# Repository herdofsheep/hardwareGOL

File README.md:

# hardwareGOL
Arduino code to run the game of life on an LED multiplex.

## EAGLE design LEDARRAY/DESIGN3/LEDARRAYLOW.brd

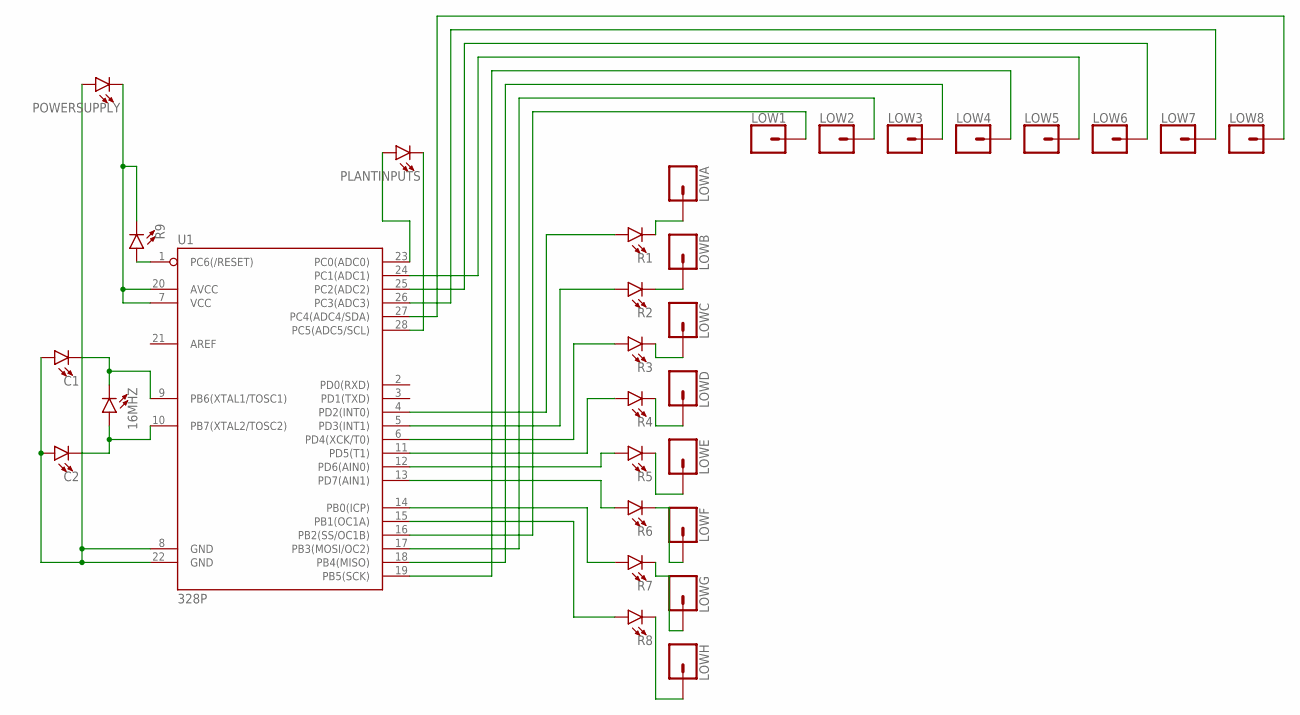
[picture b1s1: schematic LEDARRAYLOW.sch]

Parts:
16MHZ: LED3MM; LED_3MM
C1, C2: LED3MM; LED_3MM
LOW1, LOW2, LOW3, LOW4, LOW5, LOW6, LOW7, LOW8: CONN_01PTH_NO_SILK_KIT; 1X01NS_KIT
LOWA: CONN_01PTH_NO_SILK_KIT; 1X01NS_KIT
LOWB: CONN_01PTH_NO_SILK_KIT; 1X01NS_KIT
LOWC: CONN_01PTH_NO_SILK_KIT; 1X01NS_KIT
LOWD: CONN_01PTH_NO_SILK_KIT; 1X01NS_KIT
LOWE: CONN_01PTH_NO_SILK_KIT; 1X01NS_KIT
LOWF: CONN_01PTH_NO_SILK_KIT; 1X01NS_KIT
LOWG: CONN_01PTH_NO_SILK_KIT; 1X01NS_KIT
LOWH: CONN_01PTH_NO_SILK_KIT; 1X01NS_KIT
PLANTINPUTS: LED3MM; LED_3MM
POWERSUPPLY: LED3MM; LED_3MM
R1, R2, R3, R4, R5, R6, R7, R8, R9: LED3MM; LED_3MM
U1: 328P; DIP28

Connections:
LEDD1: LOW1.1, U1.16 (PB2(SS/OC1B))
unnamed: R8.A, U1.15 (PB1(OC1A))
unnamed: LOWD.1, R4.K (C)
unnamed: R6.A, U1.13 (PD7(AIN1))
unnamed: LOW6.1, U1.25 (PC2(ADC2))
unnamed: LOW2.1, U1.17 (PB3(MOSI/OC2))
unnamed: R7.A, U1.14 (PB0(ICP))
unnamed: LOW3.1, U1.18 (PB4(MISO))
unnamed: PLANTINPUTS.A, U1.23 (PC0(ADC0))
unnamed: LOW5.1, U1.24 (PC1(ADC1))
unnamed: 16MHZ.K (C), C1.K (C), U1.9 (PB6(XTAL1/TOSC1))
unnamed: R9.A, U1.1 (PC6(/RESET))
unnamed: R5.A, U1.12 (PD6(AIN0))
unnamed: R4.A, U1.11 (PD5(T1))
unnamed: LOW7.1, U1.26 (PC3(ADC3))
unnamed: LOW8.1, U1.27 (PC4(ADC4/SDA))
unnamed: R2.A, U1.5 (PD3(INT1))
unnamed: R1.A, U1.4 (PD2(INT0))
unnamed: PLANTINPUTS.K (C), U1.28 (PC5(ADC5/SCL))
unnamed: POWERSUPPLY.K (C), R9.K (C), U1.7 (VCC), U1.20 (AVCC)
unnamed: LOW4.1, U1.19 (PB5(SCK))
unnamed: 16MHZ.A, C2.K (C), U1.10 (PB7(XTAL2/TOSC2))
unnamed: LOWC.1, R3.K (C)
unnamed: R3.A, U1.6 (PD4(XCK/T0))
unnamed: LOWB.1, R2.K (C)
unnamed: LOWA.1, R1.K (C)
unnamed: LOWE.1, R5.K (C)
unnamed: LOWF.1, R6.K (C)
unnamed: LOWG.1, R7.K (C)
unnamed: LOWH.1, R8.K (C)
POWERSUPPLY: C1.A, C2.A, POWERSUPPLY.A, U1.8 (GND), U1.22 (GND)

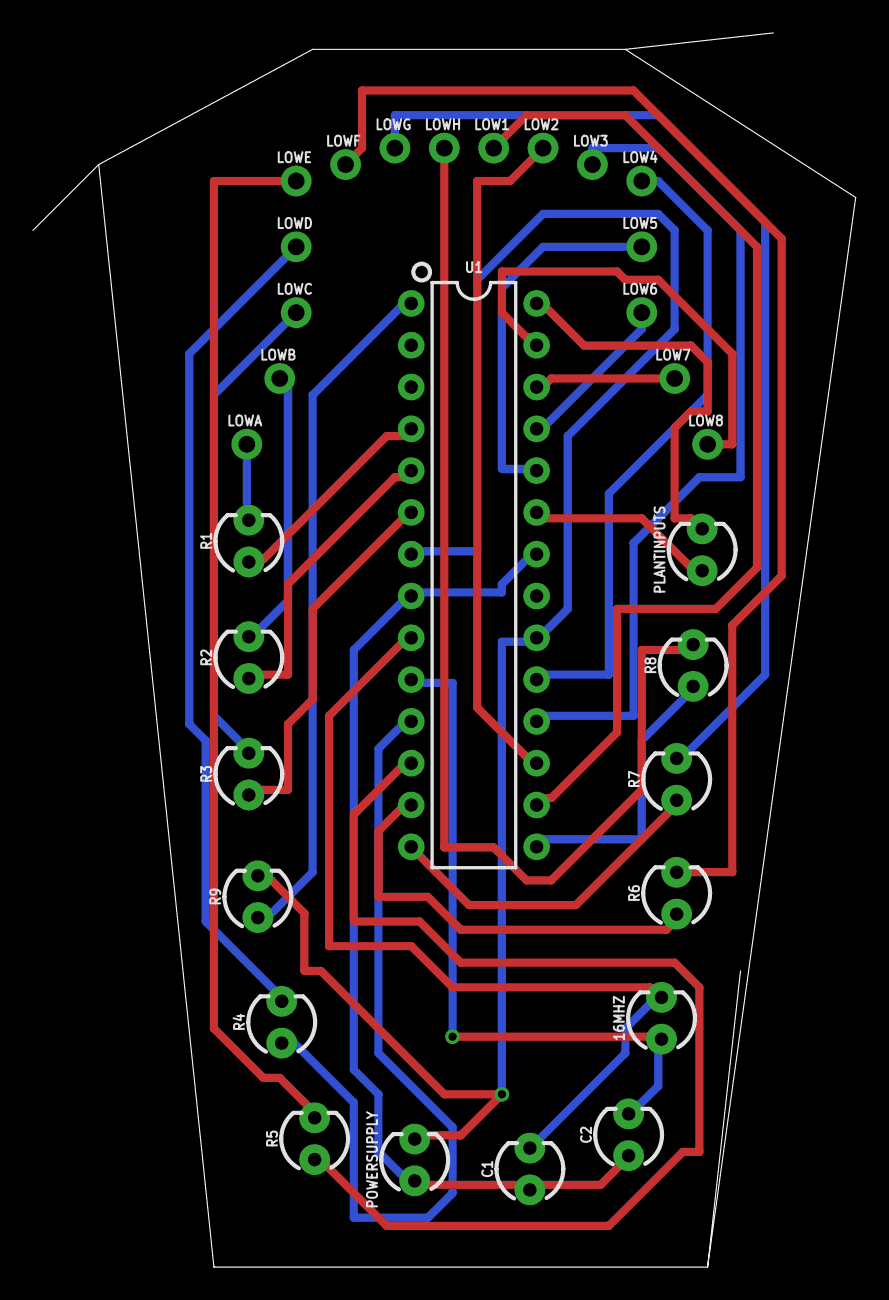
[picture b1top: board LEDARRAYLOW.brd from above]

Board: 2 copper layers, 50.0 x 75.0 mm, 31 parts (0 on the bottom side), 31 nets.

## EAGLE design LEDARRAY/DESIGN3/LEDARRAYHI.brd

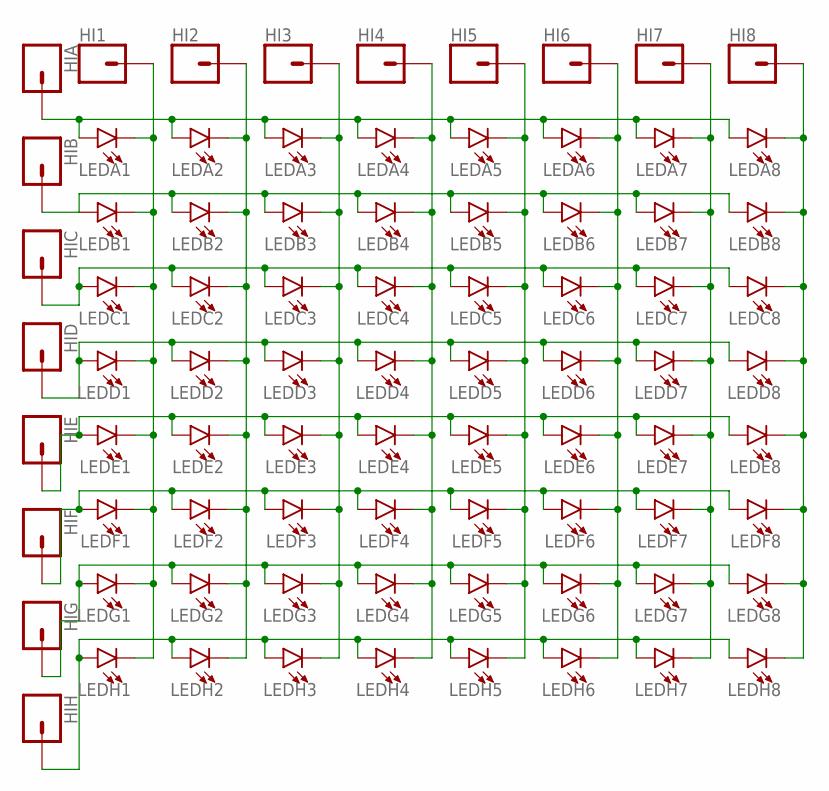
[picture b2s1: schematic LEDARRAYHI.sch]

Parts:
HI1, HI2, HI3, HI4, HI5, HI6, HI7, HI8: CONN_01PTH_NO_SILK_KIT; 1X01NS_KIT
HIA: CONN_01PTH_NO_SILK_KIT; 1X01NS_KIT
HIB: CONN_01PTH_NO_SILK_KIT; 1X01NS_KIT
HIC: CONN_01PTH_NO_SILK_KIT; 1X01NS_KIT
HID: CONN_01PTH_NO_SILK_KIT; 1X01NS_KIT
HIE: CONN_01PTH_NO_SILK_KIT; 1X01NS_KIT
HIF: CONN_01PTH_NO_SILK_KIT; 1X01NS_KIT
HIG: CONN_01PTH_NO_SILK_KIT; 1X01NS_KIT
HIH: CONN_01PTH_NO_SILK_KIT; 1X01NS_KIT
LEDA1, LEDA2, LEDA3, LEDA4, LEDA5, LEDA6, LEDA7, LEDA8: LED3MM; LED_3MM
LEDB1, LEDB2, LEDB3, LEDB4, LEDB5, LEDB6, LEDB7, LEDB8: LED3MM; LED_3MM
LEDC1, LEDC2, LEDC3, LEDC4, LEDC5, LEDC6, LEDC7, LEDC8: LED3MM; LED_3MM
LEDD1, LEDD2, LEDD3, LEDD4, LEDD5, LEDD6, LEDD7, LEDD8: LED3MM; LED_3MM
LEDE1, LEDE2, LEDE3, LEDE4, LEDE5, LEDE6, LEDE7, LEDE8: LED3MM; LED_3MM
LEDF1, LEDF2, LEDF3, LEDF4, LEDF5, LEDF6, LEDF7, LEDF8: LED3MM; LED_3MM
LEDG1, LEDG2, LEDG3, LEDG4, LEDG5, LEDG6, LEDG7, LEDG8: LED3MM; LED_3MM
LEDH1, LEDH2, LEDH3, LEDH4, LEDH5, LEDH6, LEDH7, LEDH8: LED3MM; LED_3MM

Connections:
unnamed: HIG.1, LEDG1.A, LEDG2.A, LEDG3.A, LEDG4.A, LEDG5.A, LEDG6.A, LEDG7.A, LEDG8.A
unnamed: HIF.1, LEDF1.A, LEDF2.A, LEDF3.A, LEDF4.A, LEDF5.A, LEDF6.A, LEDF7.A, LEDF8.A
unnamed: HIH.1, LEDH1.A, LEDH2.A, LEDH3.A, LEDH4.A, LEDH5.A, LEDH6.A, LEDH7.A, LEDH8.A
unnamed: HID.1, LEDD1.A, LEDD2.A, LEDD3.A, LEDD4.A, LEDD5.A, LEDD6.A, LEDD7.A, LEDD8.A
unnamed: HIB.1, LEDB1.A, LEDB2.A, LEDB3.A, LEDB4.A, LEDB5.A, LEDB6.A, LEDB7.A, LEDB8.A
unnamed: HIE.1, LEDE1.A, LEDE2.A, LEDE3.A, LEDE4.A, LEDE5.A, LEDE6.A, LEDE7.A, LEDE8.A
unnamed: HIC.1, LEDC1.A, LEDC2.A, LEDC3.A, LEDC4.A, LEDC5.A, LEDC6.A, LEDC7.A, LEDC8.A
unnamed: HIA.1, LEDA1.A, LEDA2.A, LEDA3.A, LEDA4.A, LEDA5.A, LEDA6.A, LEDA7.A, LEDA8.A
unnamed: HI1.1, LEDA1.K (C), LEDB1.K (C), LEDC1.K (C), LEDD1.K (C), LEDE1.K (C), LEDF1.K (C), LEDG1.K (C), LEDH1.K (C)
unnamed: HI2.1, LEDA2.K (C), LEDB2.K (C), LEDC2.K (C), LEDD2.K (C), LEDE2.K (C), LEDF2.K (C), LEDG2.K (C), LEDH2.K (C)
unnamed: HI3.1, LEDA3.K (C), LEDB3.K (C), LEDC3.K (C), LEDD3.K (C), LEDE3.K (C), LEDF3.K (C), LEDG3.K (C), LEDH3.K (C)
unnamed: HI4.1, LEDA4.K (C), LEDB4.K (C), LEDC4.K (C), LEDD4.K (C), LEDE4.K (C), LEDF4.K (C), LEDG4.K (C), LEDH4.K (C)
unnamed: HI5.1, LEDA5.K (C), LEDB5.K (C), LEDC5.K (C), LEDD5.K (C), LEDE5.K (C), LEDF5.K (C), LEDG5.K (C), LEDH5.K (C)
unnamed: HI6.1, LEDA6.K (C), LEDB6.K (C), LEDC6.K (C), LEDD6.K (C), LEDE6.K (C), LEDF6.K (C), LEDG6.K (C), LEDH6.K (C)
unnamed: HI7.1, LEDA7.K (C), LEDB7.K (C), LEDC7.K (C), LEDD7.K (C), LEDE7.K (C), LEDF7.K (C), LEDG7.K (C), LEDH7.K (C)
unnamed: HI8.1, LEDA8.K (C), LEDB8.K (C), LEDC8.K (C), LEDD8.K (C), LEDE8.K (C), LEDF8.K (C), LEDG8.K (C), LEDH8.K (C)

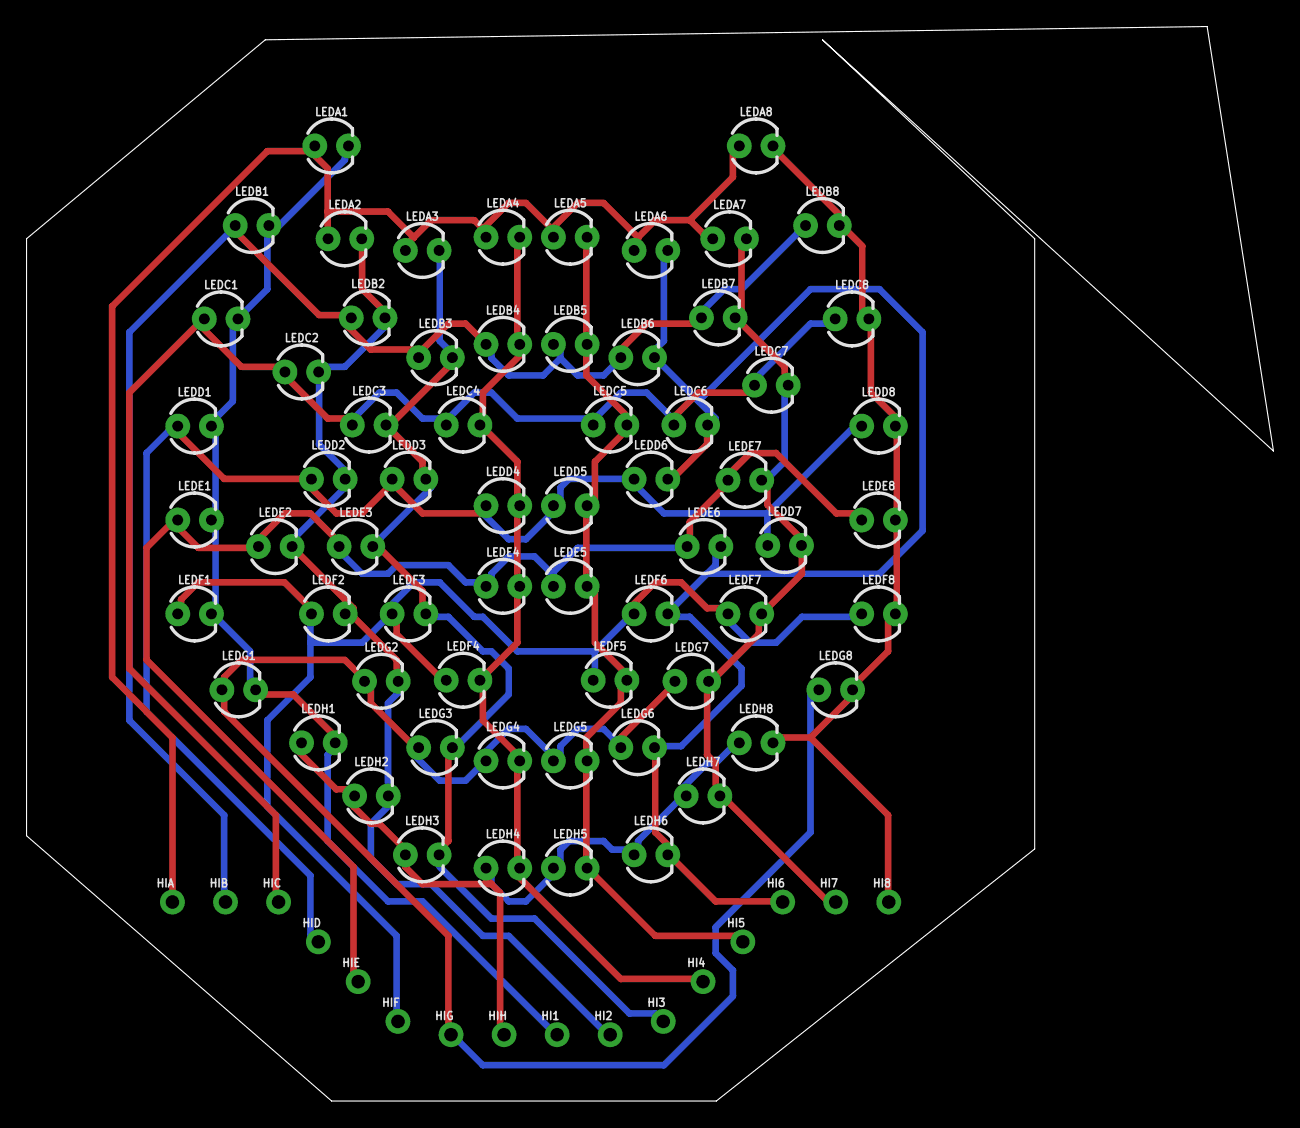
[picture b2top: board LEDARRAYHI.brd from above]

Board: 2 copper layers, 94.0 x 81.0 mm, 80 parts (0 on the bottom side), 16 nets.

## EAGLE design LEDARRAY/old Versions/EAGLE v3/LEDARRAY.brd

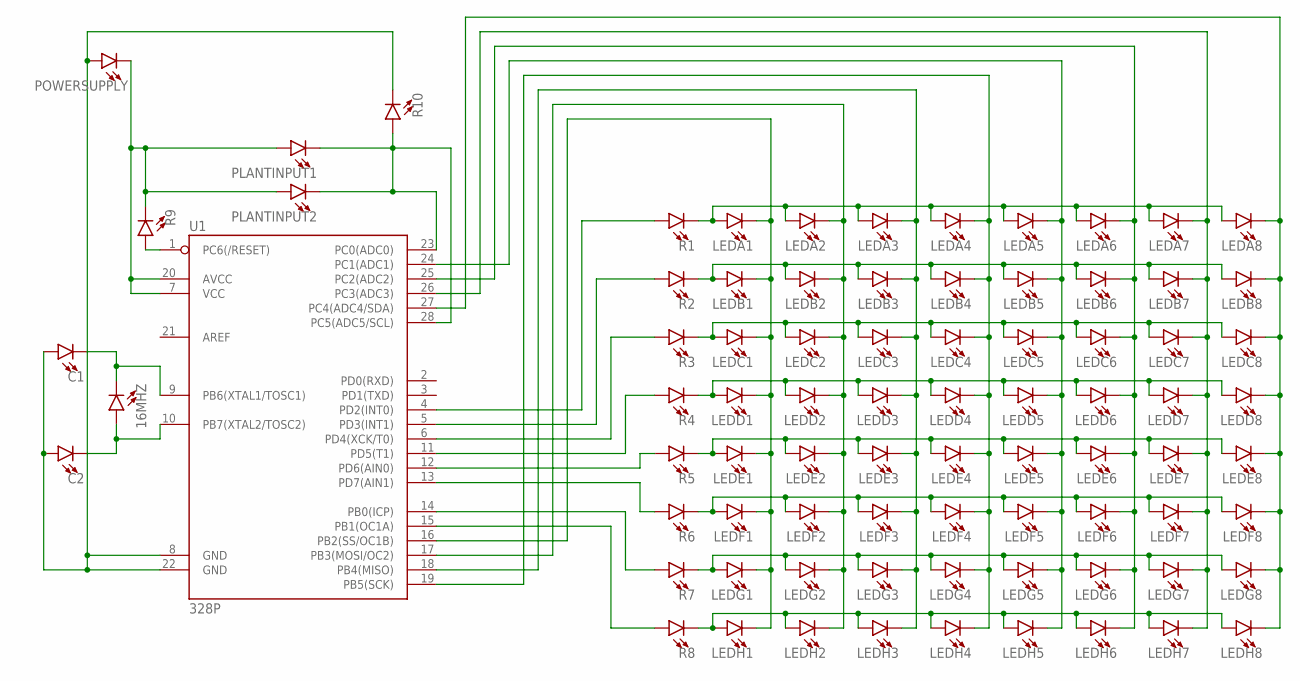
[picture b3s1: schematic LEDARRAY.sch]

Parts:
16MHZ: LED3MM; LED_3MM
C1, C2: LED3MM; LED_3MM
LEDA1, LEDA2, LEDA3, LEDA4, LEDA5, LEDA6, LEDA7, LEDA8: LED3MM; LED_3MM
LEDB1, LEDB2, LEDB3, LEDB4, LEDB5, LEDB6, LEDB7, LEDB8: LED3MM; LED_3MM
LEDC1, LEDC2, LEDC3, LEDC4, LEDC5, LEDC6, LEDC7, LEDC8: LED3MM; LED_3MM
LEDD1, LEDD2, LEDD3, LEDD4, LEDD5, LEDD6, LEDD7, LEDD8: LED3MM; LED_3MM
LEDE1, LEDE2, LEDE3, LEDE4, LEDE5, LEDE6, LEDE7, LEDE8: LED3MM; LED_3MM
LEDF1, LEDF2, LEDF3, LEDF4, LEDF5, LEDF6, LEDF7, LEDF8: LED3MM; LED_3MM
LEDG1, LEDG2, LEDG3, LEDG4, LEDG5, LEDG6, LEDG7, LEDG8: LED3MM; LED_3MM
LEDH1, LEDH2, LEDH3, LEDH4, LEDH5, LEDH6, LEDH7, LEDH8: LED3MM; LED_3MM
PLANTINPUT1, PLANTINPUT2: LED3MM; LED_3MM
POWERSUPPLY: LED3MM; LED_3MM
R1, R2, R3, R4, R5, R6, R7, R8, R9, R10: LED3MM; LED_3MM
U1: 328P; DIP28

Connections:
LEDD1: LEDA1.K (C), LEDB1.K (C), LEDC1.K (C), LEDD1.K (C), LEDE1.K (C), LEDF1.K (C), LEDG1.K (C), LEDH1.K (C), U1.16 (PB2(SS/OC1B))
unnamed: R8.A, U1.15 (PB1(OC1A))
unnamed: LEDG1.A, LEDG2.A, LEDG3.A, LEDG4.A, LEDG5.A, LEDG6.A, LEDG7.A, LEDG8.A, R7.K (C)
unnamed: LEDF1.A, LEDF2.A, LEDF3.A, LEDF4.A, LEDF5.A, LEDF6.A, LEDF7.A, LEDF8.A, R6.K (C)
unnamed: LEDH1.A, LEDH2.A, LEDH3.A, LEDH4.A, LEDH5.A, LEDH6.A, LEDH7.A, LEDH8.A, R8.K (C)
unnamed: LEDD1.A, LEDD2.A, LEDD3.A, LEDD4.A, LEDD5.A, LEDD6.A, LEDD7.A, LEDD8.A, R4.K (C)
unnamed: LEDE1.A, LEDE2.A, LEDE3.A, LEDE4.A, LEDE5.A, LEDE6.A, LEDE7.A, LEDE8.A, R5.K (C)
unnamed: R6.A, U1.13 (PD7(AIN1))
unnamed: LEDA6.K (C), LEDB6.K (C), LEDC6.K (C), LEDD6.K (C), LEDE6.K (C), LEDF6.K (C), LEDG6.K (C), LEDH6.K (C), U1.25 (PC2(ADC2))
unnamed: LEDA2.K (C), LEDB2.K (C), LEDC2.K (C), LEDD2.K (C), LEDE2.K (C), LEDF2.K (C), LEDG2.K (C), LEDH2.K (C), U1.17 (PB3(MOSI/OC2))
unnamed: R7.A, U1.14 (PB0(ICP))
unnamed: LEDA3.K (C), LEDB3.K (C), LEDC3.K (C), LEDD3.K (C), LEDE3.K (C), LEDF3.K (C), LEDG3.K (C), LEDH3.K (C), U1.18 (PB4(MISO))
unnamed: LEDB1.A, LEDB2.A, LEDB3.A, LEDB4.A, LEDB5.A, LEDB6.A, LEDB7.A, LEDB8.A, R2.K (C)
unnamed: LEDA5.K (C), LEDB5.K (C), LEDC5.K (C), LEDD5.K (C), LEDE5.K (C), LEDF5.K (C), LEDG5.K (C), LEDH5.K (C), U1.24 (PC1(ADC1))
unnamed: 16MHZ.K (C), C1.K (C), U1.9 (PB6(XTAL1/TOSC1))
unnamed: R9.A, U1.1 (PC6(/RESET))
unnamed: R5.A, U1.12 (PD6(AIN0))
unnamed: R4.A, U1.11 (PD5(T1))
unnamed: LEDA7.K (C), LEDB7.K (C), LEDC7.K (C), LEDD7.K (C), LEDE7.K (C), LEDF7.K (C), LEDG7.K (C), LEDH7.K (C), U1.26 (PC3(ADC3))
unnamed: LEDC1.A, LEDC2.A, LEDC3.A, LEDC4.A, LEDC5.A, LEDC6.A, LEDC7.A, LEDC8.A, R3.K (C)
unnamed: LEDA8.K (C), LEDB8.K (C), LEDC8.K (C), LEDD8.K (C), LEDE8.K (C), LEDF8.K (C), LEDG8.K (C), LEDH8.K (C), U1.27 (PC4(ADC4/SDA))
unnamed: R2.A, U1.5 (PD3(INT1))
unnamed: R1.A, U1.4 (PD2(INT0))
unnamed: PLANTINPUT1.K (C), PLANTINPUT2.K (C), R10.A, U1.23 (PC0(ADC0)), U1.28 (PC5(ADC5/SCL))
unnamed: PLANTINPUT1.A, PLANTINPUT2.A, POWERSUPPLY.K (C), R9.K (C), U1.7 (VCC), U1.20 (AVCC)
unnamed: LEDA4.K (C), LEDB4.K (C), LEDC4.K (C), LEDD4.K (C), LEDE4.K (C), LEDF4.K (C), LEDG4.K (C), LEDH4.K (C), U1.19 (PB5(SCK))
unnamed: 16MHZ.A, C2.K (C), U1.10 (PB7(XTAL2/TOSC2))
unnamed: R3.A, U1.6 (PD4(XCK/T0))
unnamed: LEDA1.A, LEDA2.A, LEDA3.A, LEDA4.A, LEDA5.A, LEDA6.A, LEDA7.A, LEDA8.A, R1.K (C)
POWERSUPPLY: C1.A, C2.A, POWERSUPPLY.A, R10.K (C), U1.8 (GND), U1.22 (GND)

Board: 2 copper layers, 81 parts (0 on the bottom side), 30 nets, no tracks yet.

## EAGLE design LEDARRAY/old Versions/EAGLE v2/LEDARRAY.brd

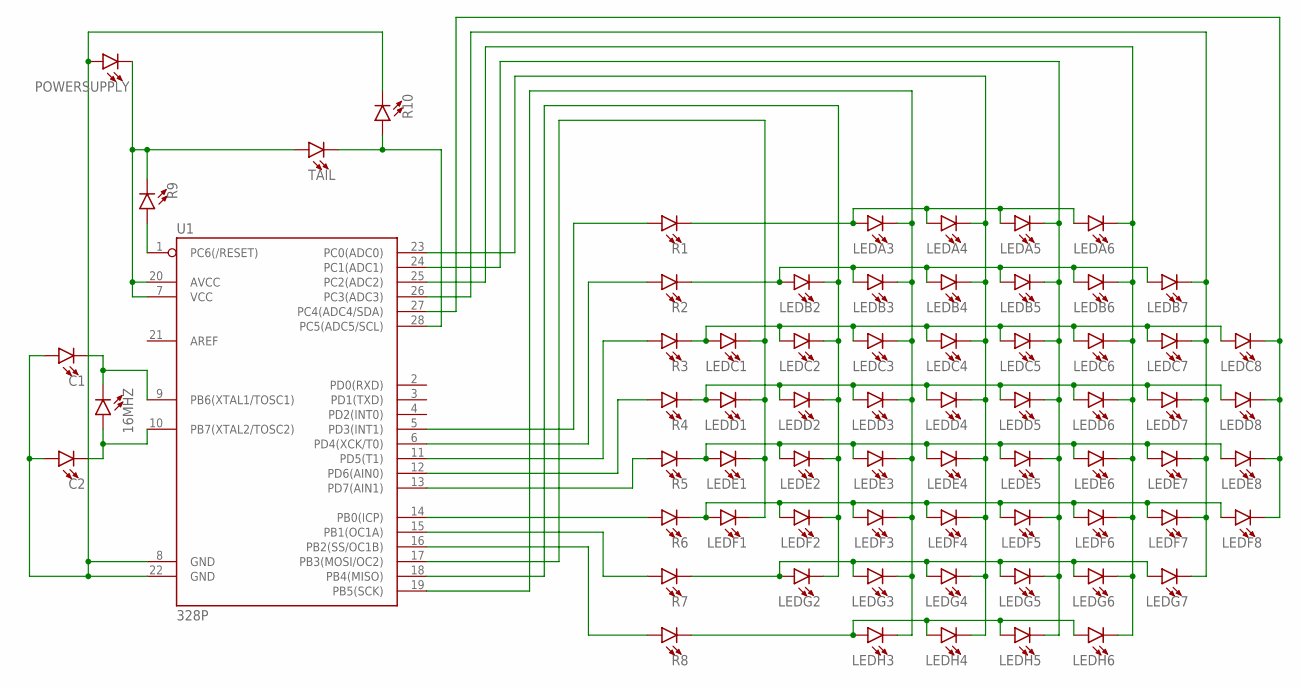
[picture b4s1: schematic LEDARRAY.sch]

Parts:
16MHZ: LED3MM; LED_3MM
C1, C2: LED3MM; LED_3MM
LEDA3, LEDA4, LEDA5, LEDA6: LED3MM; LED_3MM
LEDB2, LEDB3, LEDB4, LEDB5, LEDB6, LEDB7: LED3MM; LED_3MM
LEDC1, LEDC2, LEDC3, LEDC4, LEDC5, LEDC6, LEDC7, LEDC8: LED3MM; LED_3MM
LEDD1, LEDD2, LEDD3, LEDD4, LEDD5, LEDD6, LEDD7, LEDD8: LED3MM; LED_3MM
LEDE1, LEDE2, LEDE3, LEDE4, LEDE5, LEDE6, LEDE7, LEDE8: LED3MM; LED_3MM
LEDF1, LEDF2, LEDF3, LEDF4, LEDF5, LEDF6, LEDF7, LEDF8: LED3MM; LED_3MM
LEDG2, LEDG3, LEDG4, LEDG5, LEDG6, LEDG7: LED3MM; LED_3MM
LEDH3, LEDH4, LEDH5, LEDH6: LED3MM; LED_3MM
POWERSUPPLY: LED3MM; LED_3MM
R1, R2, R3, R4, R5, R6, R7, R8, R9, R10: LED3MM; LED_3MM
TAIL: LED3MM; LED_3MM
U1: 328P; DIP28

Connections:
LEDD1: LEDC1.K (C), LEDD1.K (C), LEDE1.K (C), LEDF1.K (C), U1.17 (PB3(MOSI/OC2))
unnamed: R8.A, U1.16 (PB2(SS/OC1B))
unnamed: LEDG2.A, LEDG3.A, LEDG4.A, LEDG5.A, LEDG6.A, LEDG7.A, R7.K (C)
unnamed: LEDF1.A, LEDF2.A, LEDF3.A, LEDF4.A, LEDF5.A, LEDF6.A, LEDF7.A, LEDF8.A, R6.K (C)
unnamed: LEDH3.A, LEDH4.A, LEDH5.A, LEDH6.A, R8.K (C)
unnamed: LEDD1.A, LEDD2.A, LEDD3.A, LEDD4.A, LEDD5.A, LEDD6.A, LEDD7.A, LEDD8.A, R4.K (C)
unnamed: LEDE1.A, LEDE2.A, LEDE3.A, LEDE4.A, LEDE5.A, LEDE6.A, LEDE7.A, LEDE8.A, R5.K (C)
unnamed: LEDA6.K (C), LEDB6.K (C), LEDC6.K (C), LEDD6.K (C), LEDE6.K (C), LEDF6.K (C), LEDG6.K (C), LEDH6.K (C), U1.25 (PC2(ADC2))
unnamed: LEDB2.K (C), LEDC2.K (C), LEDD2.K (C), LEDE2.K (C), LEDF2.K (C), LEDG2.K (C), U1.18 (PB4(MISO))
unnamed: R7.A, U1.15 (PB1(OC1A))
unnamed: LEDA3.K (C), LEDB3.K (C), LEDC3.K (C), LEDD3.K (C), LEDE3.K (C), LEDF3.K (C), LEDG3.K (C), LEDH3.K (C), U1.19 (PB5(SCK))
unnamed: LEDB2.A, LEDB3.A, LEDB4.A, LEDB5.A, LEDB6.A, LEDB7.A, R2.K (C)
unnamed: LEDA5.K (C), LEDB5.K (C), LEDC5.K (C), LEDD5.K (C), LEDE5.K (C), LEDF5.K (C), LEDG5.K (C), LEDH5.K (C), U1.24 (PC1(ADC1))
unnamed: R6.A, U1.14 (PB0(ICP))
unnamed: 16MHZ.K (C), C1.K (C), U1.9 (PB6(XTAL1/TOSC1))
unnamed: R9.A, U1.1 (PC6(/RESET))
unnamed: R5.A, U1.13 (PD7(AIN1))
unnamed: R4.A, U1.12 (PD6(AIN0))
unnamed: LEDB7.K (C), LEDC7.K (C), LEDD7.K (C), LEDE7.K (C), LEDF7.K (C), LEDG7.K (C), U1.26 (PC3(ADC3))
unnamed: LEDC1.A, LEDC2.A, LEDC3.A, LEDC4.A, LEDC5.A, LEDC6.A, LEDC7.A, LEDC8.A, R3.K (C)
unnamed: LEDC8.K (C), LEDD8.K (C), LEDE8.K (C), LEDF8.K (C), U1.27 (PC4(ADC4/SDA))
unnamed: R2.A, U1.6 (PD4(XCK/T0))
unnamed: R1.A, U1.5 (PD3(INT1))
unnamed: R10.A, TAIL.K (C), U1.28 (PC5(ADC5/SCL))
unnamed: POWERSUPPLY.K (C), R9.K (C), TAIL.A, U1.7 (VCC), U1.20 (AVCC)
unnamed: LEDA4.K (C), LEDB4.K (C), LEDC4.K (C), LEDD4.K (C), LEDE4.K (C), LEDF4.K (C), LEDG4.K (C), LEDH4.K (C), U1.23 (PC0(ADC0))
unnamed: 16MHZ.A, C2.K (C), U1.10 (PB7(XTAL2/TOSC2))
unnamed: R3.A, U1.11 (PD5(T1))
unnamed: LEDA3.A, LEDA4.A, LEDA5.A, LEDA6.A, R1.K (C)
POWERSUPPLY: C1.A, C2.A, POWERSUPPLY.A, R10.K (C), U1.8 (GND), U1.22 (GND)

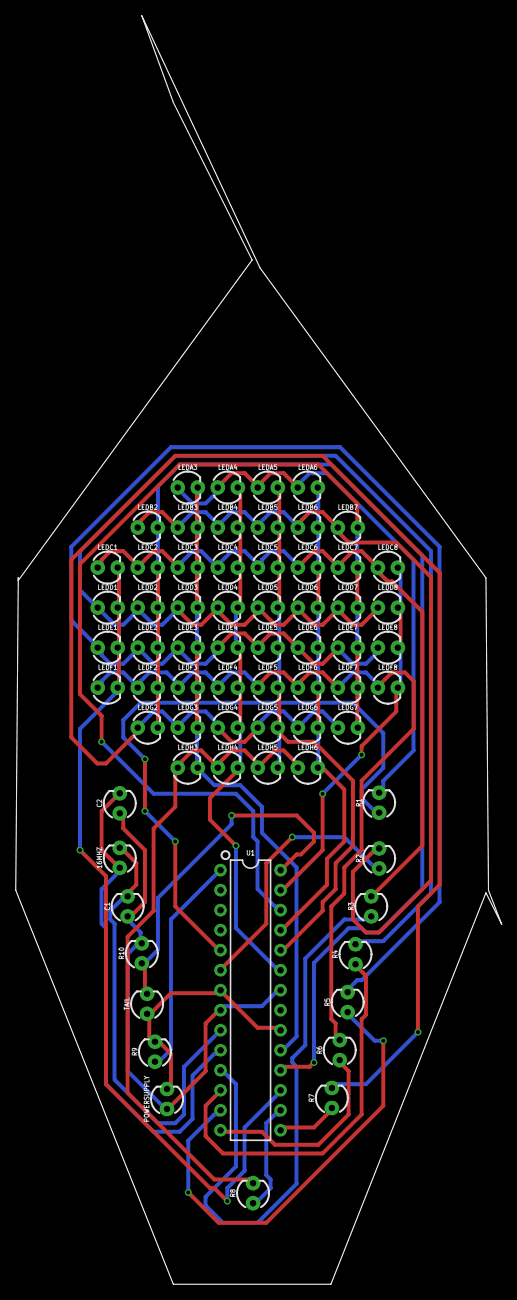
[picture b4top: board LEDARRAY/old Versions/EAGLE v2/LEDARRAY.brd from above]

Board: 2 copper layers, 61.7 x 161.0 mm, 68 parts (0 on the bottom side), 30 nets.

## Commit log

2018-05-22 added project files
2018-05-22 file restructuring
2018-06-20 Made test versions
    creating tests to fix hardware issues
2018-07-31 Final Piece Code completed.
    includes plant graphs code pieces, moved old versions to an 'old' folder, added circuitboard designs.
2018-08-10 renamed folders and restructured for clarity
2018-08-10 Created Plant Triggered Arduino GOL code
2018-08-10 added electrode triggering to GOLElectrodeTrigger, fixed broken plantsGraph processing sketch
2018-09-04 clarified names, separated trigger and GOL code
2018-10-07 Restructured files
2019-01-20 Eagle update

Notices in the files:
parts and their libraries:
SparkFun-LED: Licensing: Creative Commons ShareAlike 4.0 International - https://creativecommons.org/licenses/by-sa/4.0
